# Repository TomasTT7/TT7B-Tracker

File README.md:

# TT7B-Tracker
This is the main repository for TT7B superpressure balloon tracker. It includes the board and schematic design files for Eagle, the current firmware and a couple of python scripts for decoding telemetry.

The tracker is in detail described in these two blog posts: [The TT7B Tracker](https://tt7hab.blogspot.com/2018/09/the-tt7b-tracker.html) and [The TT7B Tracker Vol. 2](https://tt7hab.blogspot.com/2019/03/the-tt7b-tracker-vol-2.html).

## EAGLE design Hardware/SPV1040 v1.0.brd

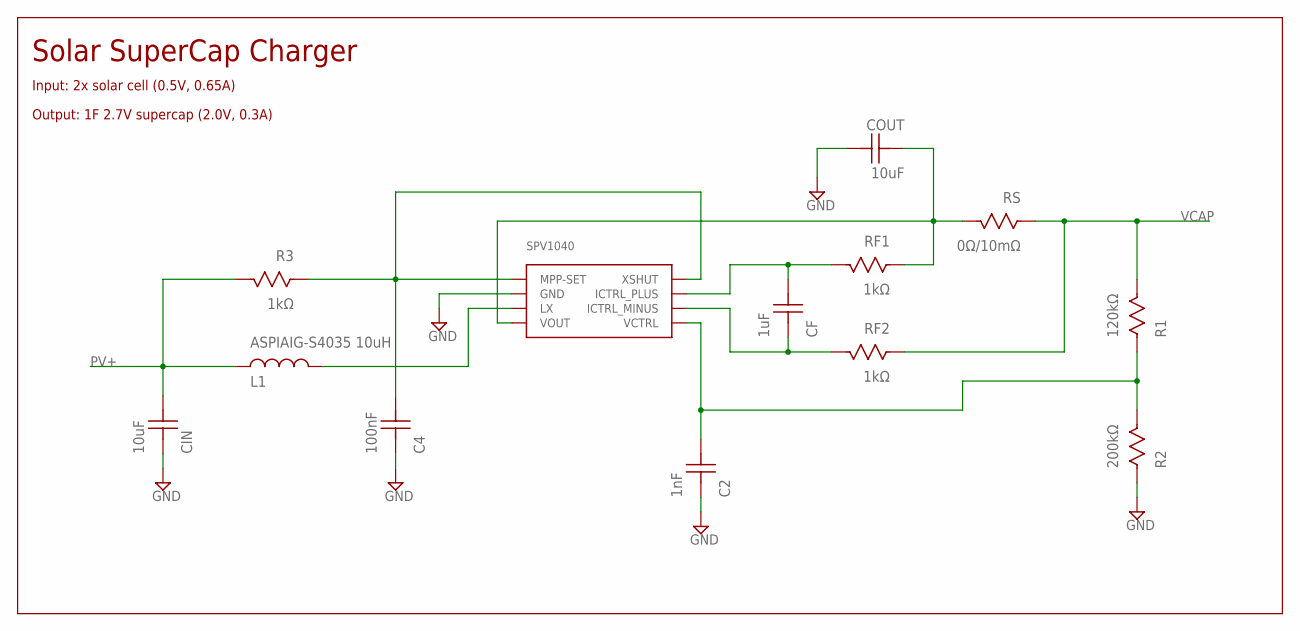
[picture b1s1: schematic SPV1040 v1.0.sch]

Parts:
C2: 1nF; CAP0402
C4: 100nF; CAP0402
CF: 1uF; CAP0402
CIN: 10uF; CAP0402
COUT: 10uF; CAP0402
L1: ASPIAIG-S4035 10uH; ASPIAIG-S4035
R1: 120kΩ; RES0402
R2: 200kΩ; RES0402
R3: 1kΩ; RES0402
RF1, RF2: 1kΩ; RES0402
RS: 0Ω/10mΩ; RES0402
U1: SPV1040

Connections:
GND: C2.P$1, C4.P$1, CIN.P$1, COUT.P$2, R2.P$1, U1.GND
N11: C4.P$2, R3.P$1, U1.MPP-SET, U1.XSHUT
unnamed: CF.P$2, RF1.P$2, U1.ICTRL_PLUS
unnamed: CF.P$1, RF2.P$2, U1.ICTRL_MINUS
unnamed: COUT.P$1, RF1.P$1, RS.P$2, U1.VOUT
unnamed: C2.P$2, R1.P$1, R2.P$2, U1.VCTRL
unnamed: L1.P$2, U1.LX
PV+: CIN.P$2, L1.P$1, R3.P$2
VCAP: R1.P$2, RF2.P$1, RS.P$1

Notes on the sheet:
Solar SuperCap Charger
Input: 2x solar cell (0.5V, 0.65A)
Output: 1F 2.7V supercap (2.0V, 0.3A)

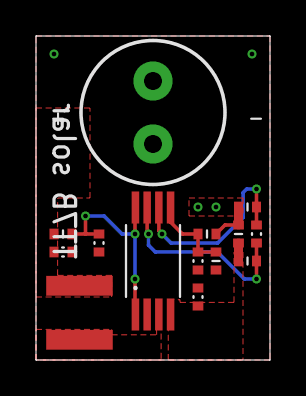
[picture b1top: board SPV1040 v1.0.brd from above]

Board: 2 copper layers, 13.0 x 18.0 mm, 13 parts (0 on the bottom side), 9 nets.

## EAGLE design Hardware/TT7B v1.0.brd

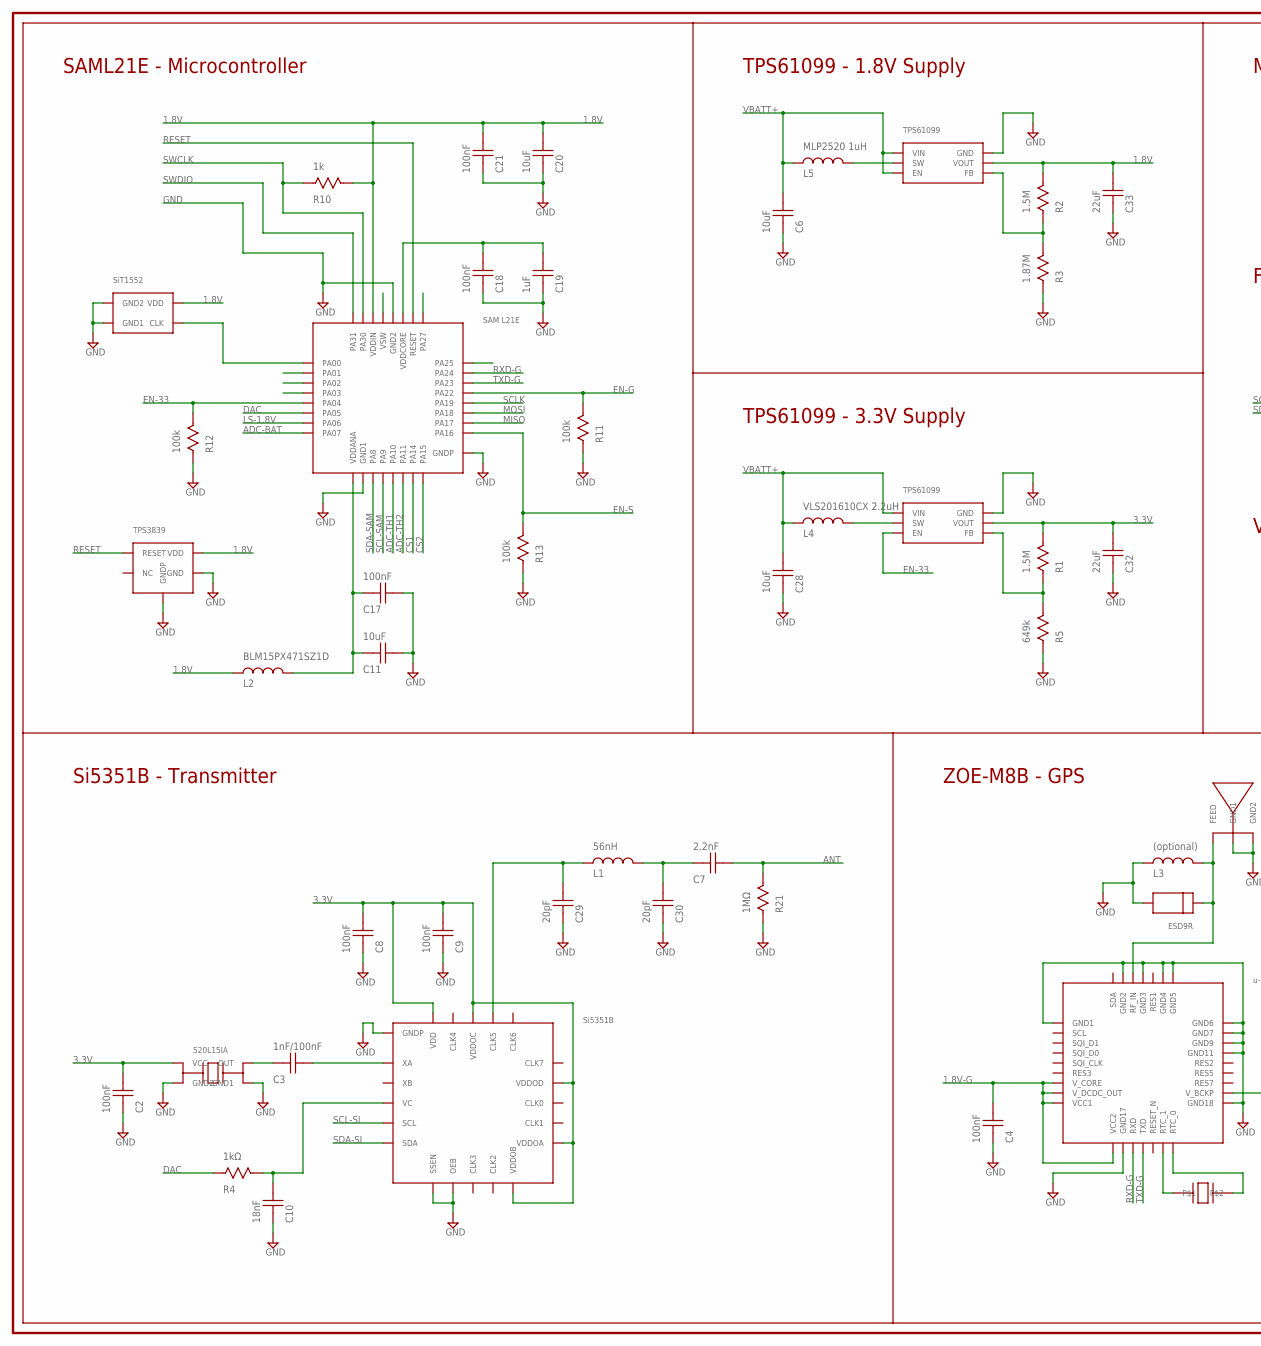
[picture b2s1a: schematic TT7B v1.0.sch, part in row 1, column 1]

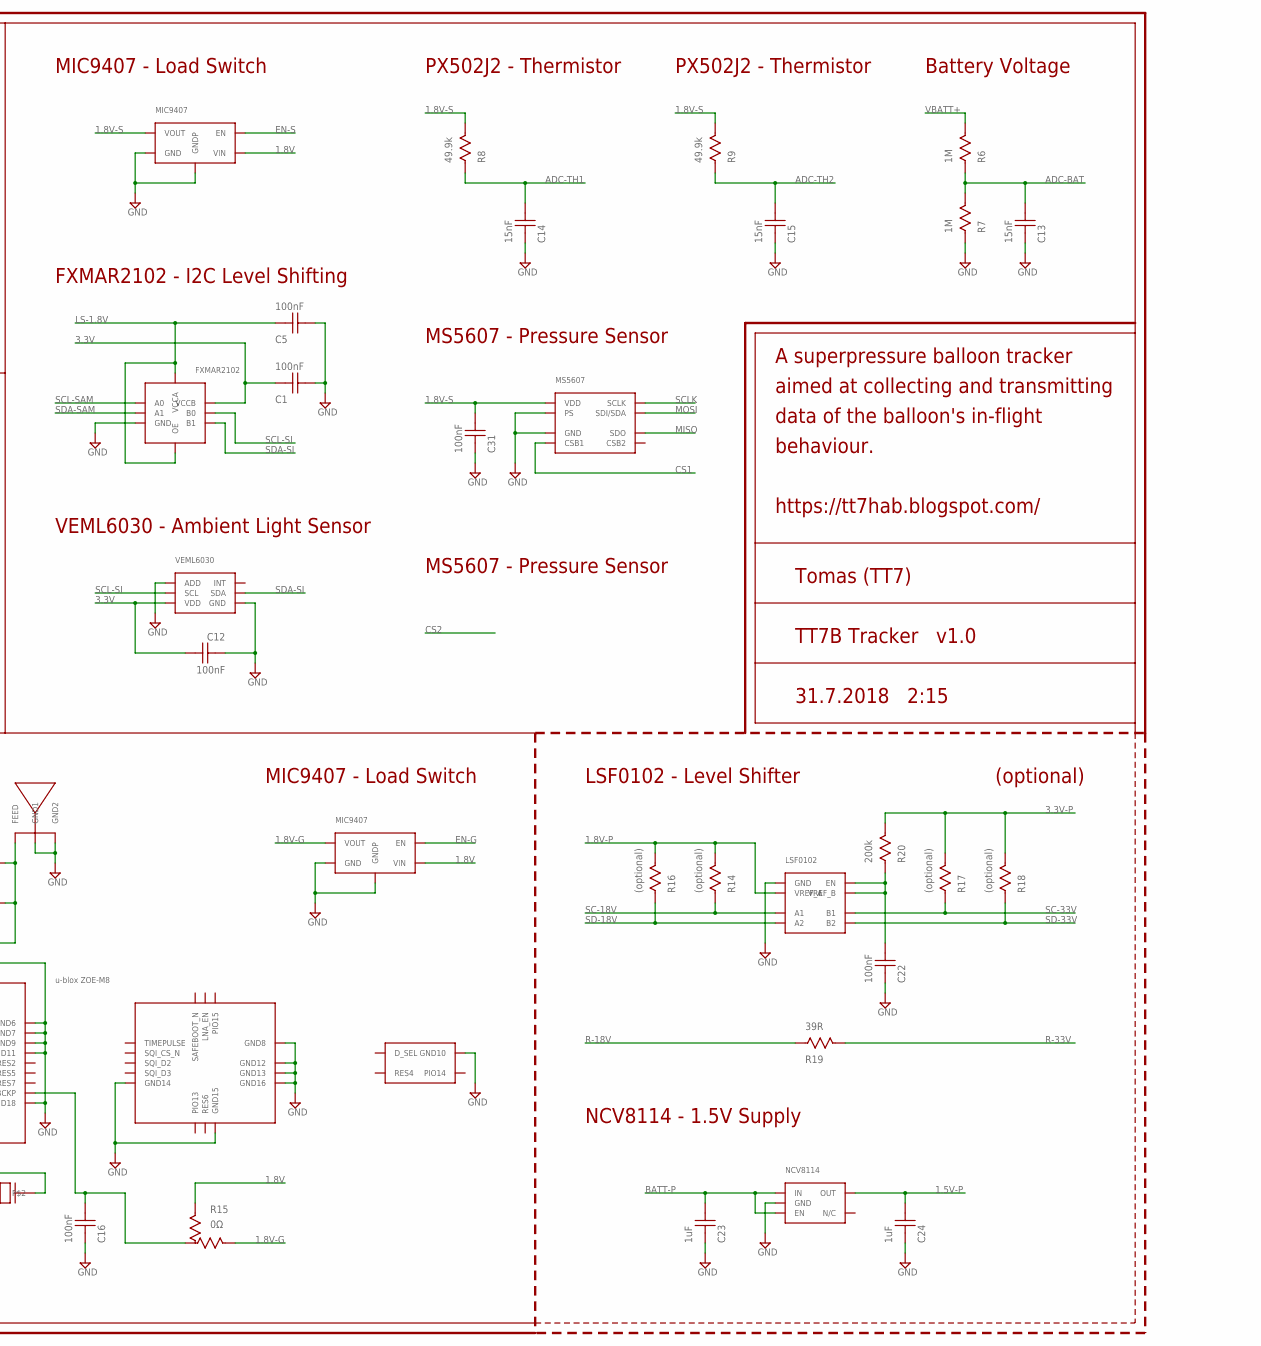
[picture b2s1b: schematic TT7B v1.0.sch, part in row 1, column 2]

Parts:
C1, C2, C4, C5, C8, C9, C12, C16, C17, C18, C21, C22, C31: 100nF; CAP0402
C3: 1nF/100nF; CAP0402
C6, C11, C20, C28: 10uF; CAP0402
C7: 2.2nF; CAP0402
C10: 18nF; CAP0402
C13, C14, C15: 15nF; CAP0402
C19, C23, C24: 1uF; CAP0402
C29, C30: 20pF; CAP0402
C32, C33: 22uF; CAP0603
D1: ESD9R
L1: 56nH; IND0402
L2: BLM15PX471SZ1D; IND0402
L3: (optional); IND0402
L4: VLS201610CX 2.2uH; VLS201610CX
L5: MLP2520 1uH; MLP2520
R1, R2: 1.5M; RES0402
R3: 1.87M; RES0402
R4: 1kΩ; RES0402
R5: 649k; RES0402
R6, R7: 1M; RES0402
R8, R9: 49.9k; RES0402
R10: 1k; RES0402
R11, R12, R13: 100k; RES0402
R14, R16, R17, R18: (optional); RES0402
R15: 0Ω; RES0402-3
R19: 39R; RES0402
R20: 200k; RES0402
R21: 1MΩ; RES0402
U1: SAML21E18B-MUT
U2: UBLOX_ZOE-M8
U3: FXMAR2102
U4: 520L15IA
U5: CM8V-T1A
U6, U13: MIC9407
U7: MS5607
U8: LSF0102
U9: NCV8114
U10: W3011A
U11: SI5351B
U12: TPS3839; TPS383
U14: SIT1552
U15: VEML6030
U16, U17: TPS61099

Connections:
1.5V-P: C24.P$2, U9.OUT
1.8V: C20.P$2, C21.P$2, C33.P$2, L2.P$1, R2.P$2, R10.P$2, R15.1, U1.VDDIN, U6.VIN, U12.VDD, U13.VIN, U14.VDD, U16.VOUT
1.8V-G: C4.P$2, R15.3, U2.VCC1, U2.VCC2, U2.V_CORE, U2.V_DCDC_OUT, U6.VOUT
1.8V-P: R14.P$2, R16.P$2, U8.VREF_A
1.8V-S: C31.P$2, R8.P$2, R9.P$2, U7.VDD, U13.VOUT
3.3V: C1.P$1, C2.P$2, C8.P$2, C9.P$2, C12.P$2, C32.P$2, R1.P$2, U3.VCCB, U4.VCC, U11.VDD, U11.VDDOA, U11.VDDOB, U11.VDDOC, U11.VDDOD, U15.VDD, U17.VOUT
3.3V-P: R17.P$2, R18.P$2, R20.P$2
ADC-BAT: C13.P$2, R6.P$1, R7.P$2, U1.PA07
ADC-TH1: C14.P$2, R8.P$1, U1.PA10
ADC-TH2: C15.P$2, R9.P$1, U1.PA11
ANT: C7.P$2, R21.P$2
BATT-P: C23.P$2, U9.EN, U9.IN
CS1: U1.PA14, U7.CSB1
CS2: U1.PA15
DAC: R4.P$1, U1.PA05
EN-33: R12.P$2, U1.PA04, U17.EN
EN-G: R11.P$2, U1.PA22, U6.EN
EN-S: R13.P$2, U1.PA16, U13.EN
GND: C1.P$2, C2.P$1, C4.P$1, C5.P$2, C6.P$1, C8.P$1, C9.P$1, C10.P$1, C11.P$2, C12.P$1, C13.P$1, C14.P$1, C15.P$1, C16.P$1, C17.P$2, C18.P$1, C19.P$1, C20.P$1, C21.P$1, C22.P$1, C23.P$1, C24.P$1, C28.P$1, C29.P$1, C30.P$1, C31.P$1, C32.P$1, C33.P$1, D1.2, L3.P$1, R3.P$1, R5.P$1, R7.P$1, R11.P$1, R12.P$1, R13.P$1, R21.P$1, U1.GND1, U1.GND2, U1.GNDP, U2.GND1, U2.GND2, U2.GND3, U2.GND4, U2.GND5, U2.GND6, U2.GND7, U2.GND8, U2.GND9, U2.GND10, U2.GND11, U2.GND12, U2.GND13, U2.GND14, U2.GND15, U2.GND16, U2.GND17, U2.GND18, U3.GND, U4.GND1, U4.GND2, U6.GND, U6.GNDP, U7.GND, U7.PS, U8.GND, U9.GND, U10.GND1, U10.GND2, U11.GNDP, U11.OEB, U11.SSEN, U12.GND, U12.GNDP, U13.GND, U13.GNDP, U14.GND1, U14.GND2, U15.ADD, U15.GND, U16.GND, U17.GND
LS-1.8V: C5.P$1, U1.PA06, U3.OE, U3.VCCA
MISO: U1.PA17, U7.SDO
MOSI: U1.PA18, U7.SDI/SDA
unnamed: D1.1, L3.P$2, U2.RF_IN, U10.FEED
unnamed: C3.P$2, U11.XA
unnamed: U2.RTC_1, U5.P$1
unnamed: U2.RTC_0, U5.P$2
unnamed: C16.P$2, R15.2, U2.V_BCKP
unnamed: C18.P$2, C19.P$2, U1.VDDCORE
unnamed: C22.P$2, R20.P$1, U8.EN, U8.VREF_B
unnamed: C11.P$1, C17.P$1, L2.P$2, U1.VDDANA
unnamed: C7.P$1, C30.P$2, L1.P$2
unnamed: R2.P$1, R3.P$2, U16.FB
unnamed: R1.P$1, R5.P$2, U17.FB
unnamed: L4.P$2, U17.SW
unnamed: L5.P$2, U16.SW
unnamed: C29.P$2, L1.P$1, U11.CLK5
unnamed: C3.P$1, U4.OUT
unnamed: C10.P$2, R4.P$2, U11.VC
R-18V: R19.P$1
R-33V: R19.P$2
RESET: U1.RESET, U12.RESET
RXD-G: U1.PA24, U2.RXD
SC-18V: R14.P$1, U8.A1
SC-33V: R17.P$1, U8.B1
SCL-SAM: U1.PA09 (PA9), U3.A0
SCL-SI: U3.B0, U11.SCL, U15.SCL
SCLK: U1.PA19, U7.SCLK
SD-18V: R16.P$1, U8.A2
SD-33V: R18.P$1, U8.B2
SDA-SAM: U1.PA08 (PA8), U3.A1
SDA-SI: U3.B1, U11.SDA, U15.SDA
SWCLK: R10.P$1, U1.PA30
SWDIO: U1.PA31
TXD-G: U1.PA23, U2.TXD
VBATT+: C6.P$2, C28.P$2, L4.P$1, L5.P$1, R6.P$2, U16.EN, U16.VIN, U17.VIN
XIN32: U1.PA00, U14.CLK

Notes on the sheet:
Battery Voltage
PX502J2 - Thermistor
MS5607 - Pressure Sensor
MIC9407 - Load Switch
VEML6030 - Ambient Light Sensor
FXMAR2102 - I2C Level Shifting
Si5351B - Transmitter
SAML21E - Microcontroller
ZOE-M8B - GPS
TPS61099 - 3.3V Supply
TPS61099 - 1.8V Supply
LSF0102 - Level Shifter
NCV8114 - 1.5V Supply
TT7B Tracker v1.0
Tomas (TT7)
31.7.2018 2:15
A superpressure balloon tracker
aimed at collecting and transmitting
data of the balloon's in-flight
behaviour.
https://tt7hab.blogspot.com/
(optional)

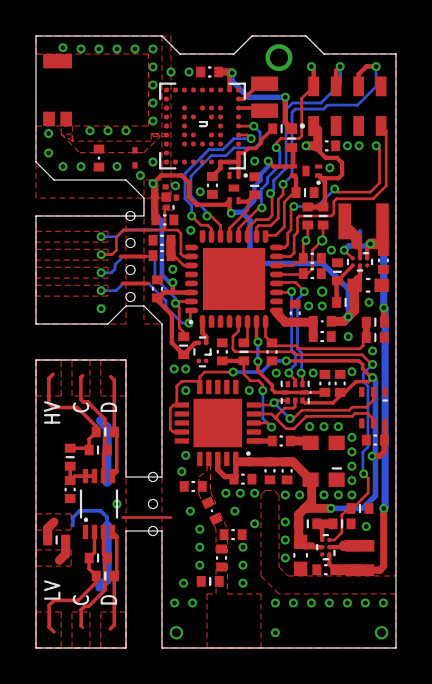
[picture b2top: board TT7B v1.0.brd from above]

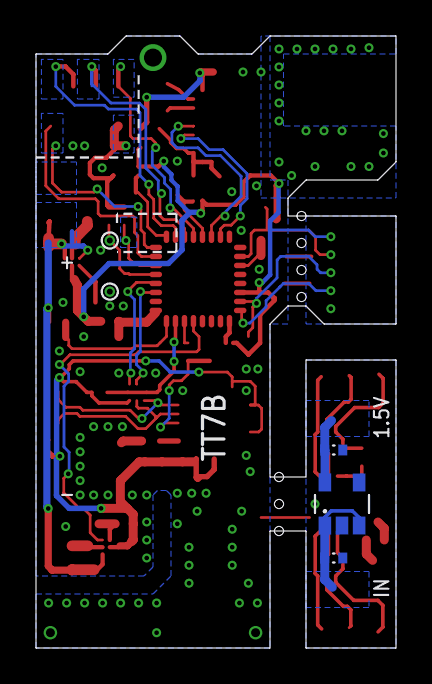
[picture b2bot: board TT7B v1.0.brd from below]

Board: 2 copper layers, 20.0 x 34.0 mm, 74 parts (3 on the bottom side), 52 nets.

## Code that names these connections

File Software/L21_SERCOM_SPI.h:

/*
	The serial peripheral interface (SPI) is one of the available modes in the Serial Communication Interface (SERCOM).
	
	TT7B TRACKER
		PA14	CS1		GPIO			-			-
		PA15	CS2		GPIO			-			-
		PA17	MISO	SERCOM 1/3		Pad[1]		Peripheral function C/D
		PA18	MOSI	SERCOM 1/3		Pad[2]		Peripheral function C/D
		PA19	SCLK	SERCOM 1/3		Pad[3]		Peripheral function C/D
*/


#ifndef L21_SERCOM_SPI_H
#define L21_SERCOM_SPI_H


#include "stdint.h"


// Functions
void SERCOM_SPI_enable(void);
void SERCOM_SPI_disable(void);
void SERCOM_SPI_reset(void);
uint8_t SERCOM_SPI_transmission(uint8_t data);


#endif // L21_SERCOM_SPI_H_

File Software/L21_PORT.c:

/*
	The IO Pin Controller (PORT) controls the I/O pins of the device.
	
	After reset, all standard function device I/O pads are connected to the PORT with outputs
	tri-stated and input buffers disabled, even if there is no clock running.
	
	PIN CONFIGURATIONS
		DIR		INEN	PULLEN	OUT		Configuration
		0		0		0		X		Reset or analog I/O: all digital disabled
		0		0		1		0		Pull-down; input disabled
		0		0		1		1		Pull-up; input disabled
		0		1		0		X		Input
		0		1		1		0		Input with pull-down
		0		1		1		1		Input with pull-up
		1		0		X		X		Output; input disabled
		1		1		X		X		Output; input enabled
*/


#include "sam.h"
#include "L21_PORT.h"


/*	
	SWTCH
	1		Load Switch - GPS			PA22		(external pull-down)
	2		Load Switch - Sensors		PA16		(external pull-down)
	3		Boost Converter - 3.3V		PA04		(external pull-down)
	4		Voltage Translator			PA06		(serves as 1.8V power supply)
*/
void PORT_switch_enable(uint8_t swtch)
{
	switch(swtch)
	{
		case 1:
			PORT->Group[0].DIRSET.reg = PORT_PA22;				// I/O pin in the PORT group is configured as an OUTPUT.
			PORT->Group[0].OUTSET.reg = PORT_PA22;				// Pin output is driven HIGH, or input is connected to an internal PULL-UP.
			break;
			
		case 2:
			PORT->Group[0].DIRSET.reg = PORT_PA16;				// I/O pin in the PORT group is configured as an OUTPUT.
			PORT->Group[0].OUTSET.reg = PORT_PA16;				// Pin output is driven HIGH, or input is connected to an internal PULL-UP.
			break;
			
		case 3:
			PORT->Group[0].DIRSET.reg = PORT_PA04;				// I/O pin in the PORT group is configured as an OUTPUT.
			PORT->Group[0].OUTSET.reg = PORT_PA04;				// Pin output is driven HIGH, or input is connected to an internal PULL-UP.
			break;
			
		case 4:
			PORT->Group[0].PINCFG[6].reg = (0x1 << 6);			// DRVSTR - Pin drive strength is set to stronger drive strength.
			PORT->Group[0].DIRSET.reg = PORT_PA06;				// I/O pin in the PORT group is configured as an OUTPUT.
			PORT->Group[0].OUTSET.reg = PORT_PA06;				// Pin output is driven HIGH, or input is connected to an internal PULL-UP.
			break;
			
		default:
			break;
	}
}


/*
	SWTCH
	1		Load Switch - GPS			PA22		(external pull-down)
	2		Load Switch - Sensors		PA16		(external pull-down)
	3		Boost Converter - 3.3V		PA04		(external pull-down)
	4		Voltage Translator			PA06		(serves as 1.8V power supply)
*/
void PORT_switch_disable(uint8_t swtch)
{
	switch(swtch)
	{
		case 1:
			PORT->Group[0].OUTCLR.reg = PORT_PA22;				// Pin output is driven LOW, or input is connected to an internal PULL-DOWN.
			PORT->Group[0].DIRCLR.reg = PORT_PA22;				// I/O pin in the PORT group is configured as an INPUT.
			break;
			
		case 2:
			PORT->Group[0].OUTCLR.reg = PORT_PA16;				// Pin output is driven LOW, or input is connected to an internal PULL-DOWN.
			PORT->Group[0].DIRCLR.reg = PORT_PA16;				// I/O pin in the PORT group is configured as an INPUT.
			break;
			
		case 3:
			PORT->Group[0].OUTCLR.reg = PORT_PA04;				// Pin output is driven LOW, or input is connected to an internal PULL-DOWN.
			PORT->Group[0].DIRCLR.reg = PORT_PA04;				// I/O pin in the PORT group is configured as an INPUT.
			break;
			
		case 4:
			PORT->Group[0].OUTCLR.reg = PORT_PA06;				// Pin output is driven LOW, or input is connected to an internal PULL-DOWN.
			PORT->Group[0].DIRCLR.reg = PORT_PA06;				// I/O pin in the PORT group is configured as an INPUT.
			break;
			
		default:
			break;
	}
}

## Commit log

2018-09-06 Create temp
2018-10-30 Create Accessories
